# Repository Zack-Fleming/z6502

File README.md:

#Z6502

This is a collection of PCBs for a 6502-based computer. The core design of the computer is based on Ben Eater's design [here](https://eater.net/6502). I will be implementing changed to the original changes in the form of version revisions. Each board revision will have its own in-depth README.md, that will go over the changes in more depth and provide other relevant information.

This project was made using the KiCAD software, that can be downloaded [here](https://www.kicad.org/download/). If you do not have KiCAD, then there is also a zip file of the Gerber and Drill files needed to order a PCB. This zip file can be uploaded to any PCB manufacturer with no problem. 

Below the use of pinheaders is mentioned on different occasions, all of these pinheaders are of the 2.54mm pitch variety, and are the same used in the Arduino or Raspberry Pi boards as well. 

## Project Use

Use of this project is encouraged, as this is 'open-source'. I just ask to give credit to this project. 

I would like to know what others create for this project. 

## Revisions at a Glance

Revision V1:

The main changes of this version are the addition of data and control bus readouts, in the form of LEDs and pinheaders. Another change was to add PCB footprins for DIP-8 and DIP-14 type oscillators.

Currently planed Revisions:
- v2: adding a clock switching, clock dividing, halt switch, and power switch
- v3: adding another VIA chip (adding two more I/O ports)
- v4: removing the bus readouts, for miniaturization

## Modules

The computer features two 8-bit ports, that have their own headers for I/O modules. The silkscreen of the board will include all of the information for the design of the modules. This information includes: the position and size of the mounting holes, the length and width of the boards, and the position of the interface pin header. Both I/O ports are situated next to each other, and are identical in dimensions. If an I/O device needs to use both of the available ports, then one can just design a board that combines the two ports into a single board. There is no need to keep the device to only one port. 

I am currently working on a template project for KiCAD, where you can create a project from the template, instead of copy pasting the project multiple times.

Currently planed modules include:
- 1602A 16x2 character LCD screen
- 8x8 button matrix 'keyboard'
- clock switching (not an I/O module)
- LED matrix ??x??
- more.

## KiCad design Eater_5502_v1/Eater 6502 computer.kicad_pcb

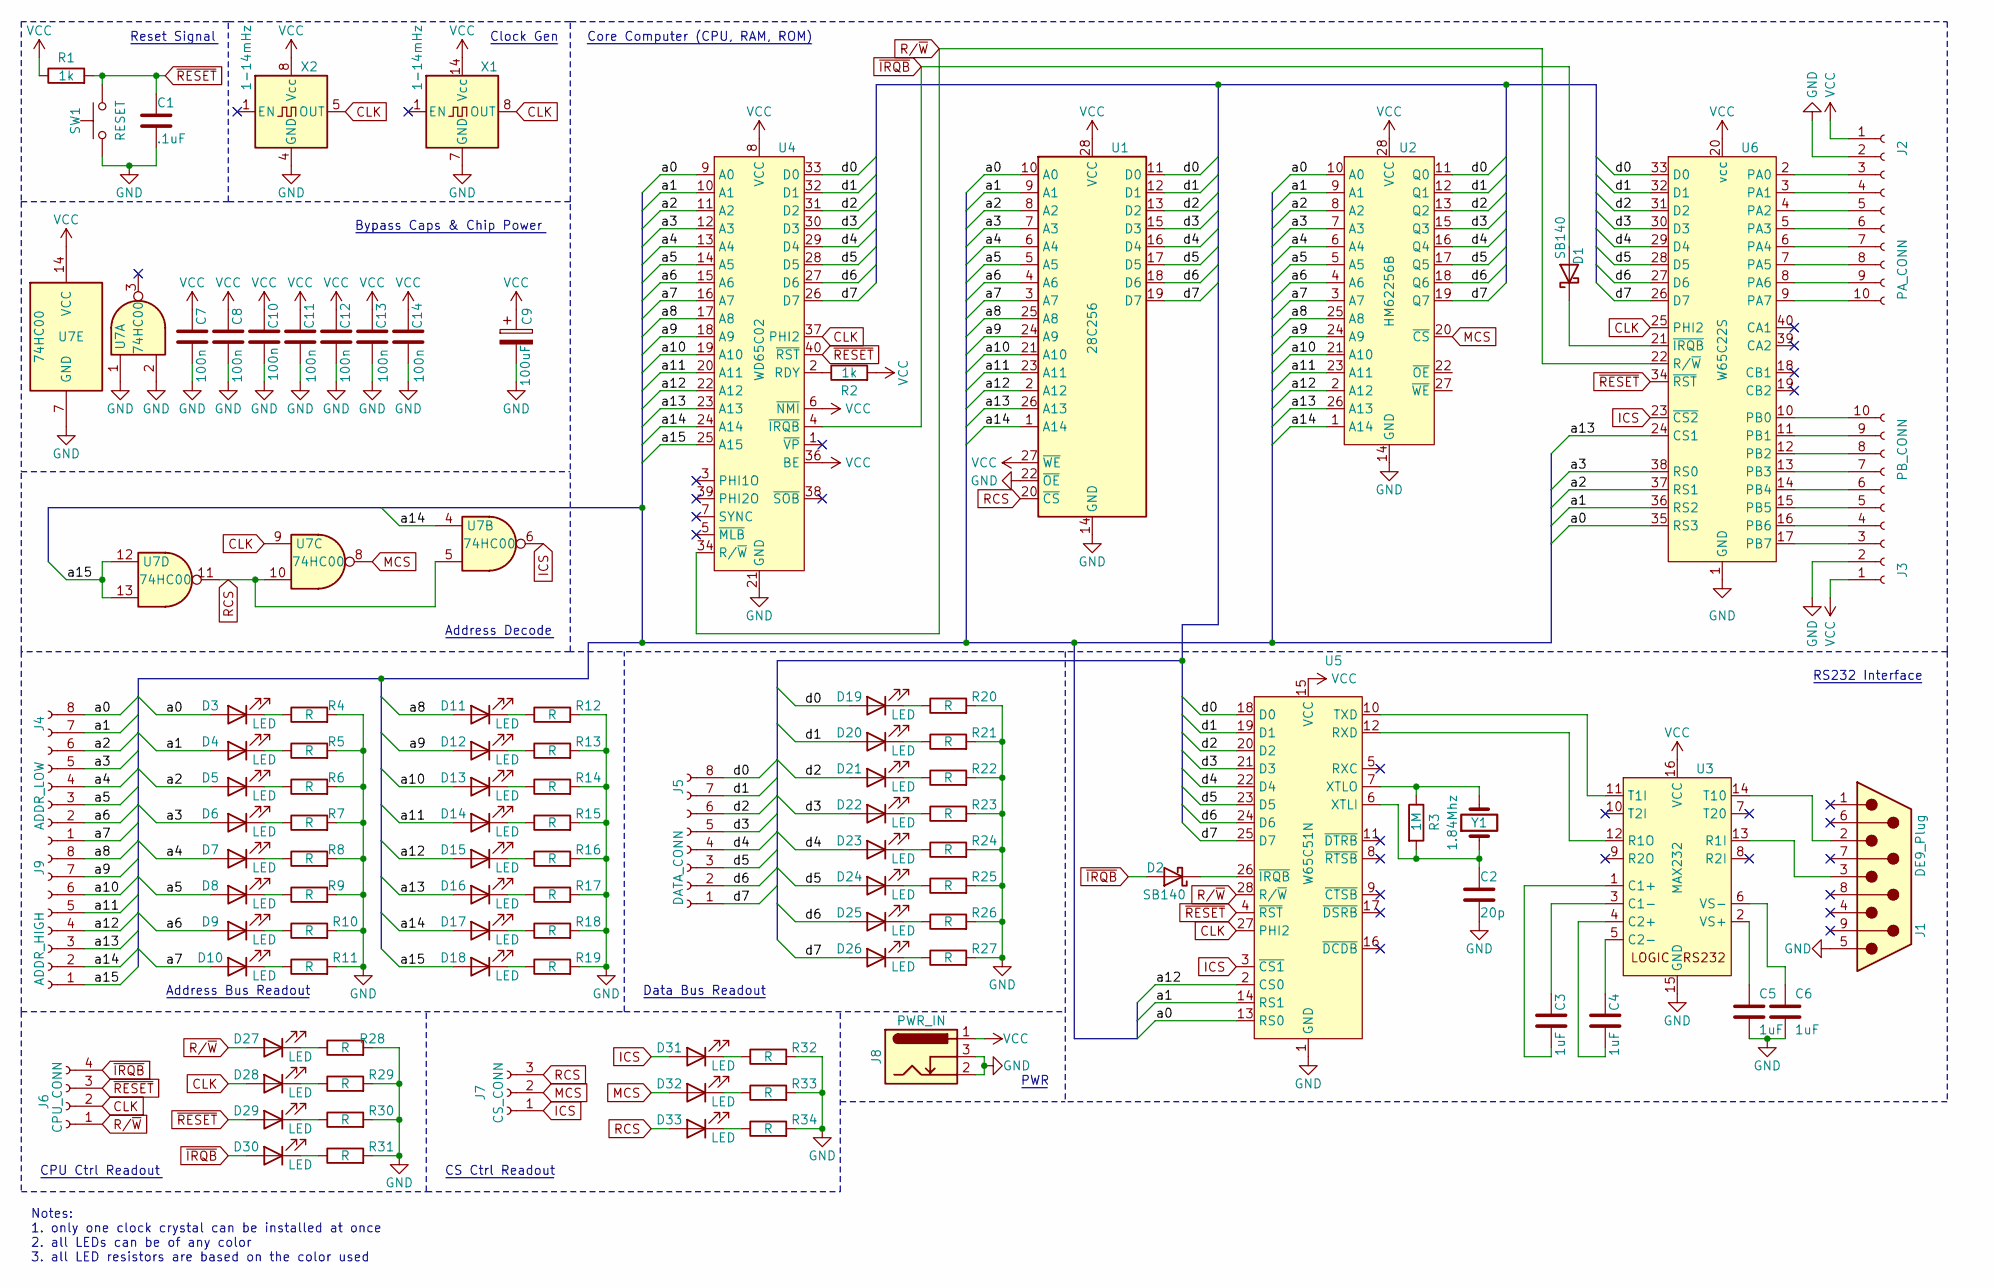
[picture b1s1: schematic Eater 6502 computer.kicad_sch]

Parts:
C1: .1uF; C_Disc_D5.0mm_W2.5mm_P5.00mm
C2: 20p; C_Disc_D5.0mm_W2.5mm_P5.00mm
C3, C4, C5, C6: 1uF; C_Disc_D5.0mm_W2.5mm_P5.00mm
C7, C8, C10, C11, C12, C13, C14: 100n; C_Disc_D5.0mm_W2.5mm_P5.00mm
C9: 100uF; CP_Radial_D5.0mm_P2.00mm
D1, D2: SB140; D_DO-41_SOD81_P10.16mm_Horizontal
D3, D4, D5, D6, D7, D8, D9, D10, D11, D12, D13, D14, D15, D16, D17, D18, D19, D20, D21, D22, D23, D24, D25, D26, D27, D28, D29, D30, D31, D32, D33: LED; LED_D5.0mm
J1: DE9_Plug; DSUB-9_Female_Horizontal_P2.77x2.84mm_EdgePinOffset9.90mm_H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
J2: PA_CONN; PinHeader_1x10_P2.54mm_Vertical
J3: PB_CONN; PinHeader_1x10_P2.54mm_Vertical
J4: ADDR_LOW; PinHeader_1x08_P2.54mm_Vertical
J5: DATA_CONN; PinHeader_1x08_P2.54mm_Vertical
J6: CPU_CONN; PinHeader_1x04_P2.54mm_Vertical
J7: CS_CONN; PinHeader_1x03_P2.54mm_Vertical
J8: PWR_IN; BarrelJack_GCT_DCJ200-10-A_Horizontal
J9: ADDR_HIGH; PinHeader_1x08_P2.54mm_Vertical
R1, R2: 1k; R_Axial_DIN0207_L6.3mm_D2.5mm_P2.54mm_Vertical
R3: 1M; R_Axial_DIN0207_L6.3mm_D2.5mm_P2.54mm_Vertical
R4, R5, R6, R7, R8, R9, R10, R11, R12, R13, R14, R15, R16, R17, R18, R19, R20, R21, R22, R23, R24, R25, R26, R27, R28, R29, R30, R31, R32, R33, R34: R; R_Axial_DIN0207_L6.3mm_D2.5mm_P2.54mm_Vertical
SW1: RESET; SW_PUSH_6mm
U1: 28C256; DIP-28_W15.24mm_Socket_LongPads
U2: HM62256B; DIP-28_W15.24mm_Socket_LongPads
U3: MAX232; DIP-16_W7.62mm_Socket_LongPads
U4: WD65C02; DIP-40_W15.24mm_Socket_LongPads
U5: W65C51N; DIP-28_W15.24mm_Socket_LongPads
U6: W65C22S; DIP-40_W15.24mm_Socket_LongPads
U7: 74HC00; DIP-14_W7.62mm_Socket_LongPads
X1: 1-14mHz; Oscillator_DIP-14
X2: 1-14mHz; Oscillator_DIP-8
Y1: 1.84Mhz; Crystal_HC49-4H_Vertical

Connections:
/a0: D3.2 (A), J4.8, U1.10 (A0), U2.10 (A0), U4.9 (A0), U5.13 (RS0), U6.35 (RS3)
/a1: D4.2 (A), J4.7, U1.9 (A1), U2.9 (A1), U4.10 (A1), U5.14 (RS1), U6.36 (RS2)
/a2: D5.2 (A), J4.6, U1.8 (A2), U2.8 (A2), U4.11 (A2), U6.37 (RS1)
/a3: D6.2 (A), J4.5, U1.7 (A3), U2.7 (A3), U4.12 (A3), U6.38 (RS0)
/a4: D7.2 (A), J4.4, U1.6 (A4), U2.6 (A4), U4.13 (A4)
/a5: D8.2 (A), J4.3, U1.5 (A5), U2.5 (A5), U4.14 (A5)
/a6: D9.2 (A), J4.2, U1.4 (A6), U2.4 (A6), U4.15 (A6)
/a7: D10.2 (A), J4.1, U1.3 (A7), U2.3 (A7), U4.16 (A7)
/a8: D11.2 (A), J9.8, U1.25 (A8), U2.25 (A8), U4.17 (A8)
/a9: D12.2 (A), J9.7, U1.24 (A9), U2.24 (A9), U4.18 (A9)
/a10: D13.2 (A), J9.6, U1.21 (A10), U2.21 (A10), U4.19 (A10)
/a11: D14.2 (A), J9.5, U1.23 (A11), U2.23 (A11), U4.20 (A11)
/a12: D15.2 (A), J9.4, U1.2 (A12), U2.2 (A12), U4.22 (A12), U5.2 (CS0)
/a13: D16.2 (A), J9.3, U1.26 (A13), U2.26 (A13), U4.23 (A13), U6.24 (CS1)
/a14: D17.2 (A), J9.2, U1.1 (A14), U2.1 (A14), U4.24 (A14), U7.4
/a15: D18.2 (A), J9.1, U4.25 (A15), U7.12, U7.13
/d0: D19.2 (A), J5.8, U1.11 (D0), U2.11 (Q0), U4.33 (D0), U5.18 (D0), U6.33 (D0)
/d1: D20.2 (A), J5.7, U1.12 (D1), U2.12 (Q1), U4.32 (D1), U5.19 (D1), U6.32 (D1)
/d2: D21.2 (A), J5.6, U1.13 (D2), U2.13 (Q2), U4.31 (D2), U5.20 (D2), U6.31 (D2)
/d3: D22.2 (A), J5.5, U1.15 (D3), U2.15 (Q3), U4.30 (D3), U5.21 (D3), U6.30 (D3)
/d4: D23.2 (A), J5.4, U1.16 (D4), U2.16 (Q4), U4.29 (D4), U5.22 (D4), U6.29 (D4)
/d5: D24.2 (A), J5.3, U1.17 (D5), U2.17 (Q5), U4.28 (D5), U5.23 (D5), U6.28 (D5)
/d6: D25.2 (A), J5.2, U1.18 (D6), U2.18 (Q6), U4.27 (D6), U5.24 (D6), U6.27 (D6)
/d7: D26.2 (A), J5.1, U1.19 (D7), U2.19 (Q7), U4.26 (D7), U5.25 (D7), U6.26 (D7)
CLK: D28.2 (A), J6.2, U4.37 (PHI2), U5.27 (PHI2), U6.25 (PHI2), U7.9, X1.8 (OUT), X2.5 (OUT)
GND: C1.2, C2.2, C5.2, C6.2, C7.2, C8.2, C9.2, C10.2, C11.2, C12.2, C13.2, C14.2, J1.0, J1.5, J2.2, J3.2, J8.2, J8.3, R4.2, R5.2, R6.2, R7.2, R8.2, R9.2, R10.2, R11.2, R12.2, R13.2, R14.2, R15.2, R16.2, R17.2, R18.2, R19.2, R20.2, R21.2, R22.2, R23.2, R24.2, R25.2, R26.2, R27.2, R28.2, R29.2, R30.2, R31.2, R32.2, R33.2, R34.2, SW1.1, U1.14 (GND), U1.22 (~OE), U2.14 (GND), U3.15 (GND), U4.21 (GND), U5.1 (GND), U6.1 (GND), U7.1, U7.2, U7.7 (GND), X1.7 (GND), X2.4 (GND)
ICS: D31.2 (A), J7.1, U5.3 (~CS1), U6.23 (~CS2), U7.6
MCS: D32.2 (A), J7.2, U2.20 (~CS), U7.8
unnamed: D1.1 (K), U6.21 (~IRQB)
unnamed: D2.1 (K), U5.26 (~IRQB)
unnamed: D3.1 (K), R4.1
unnamed: D4.1 (K), R5.1
unnamed: D5.1 (K), R6.1
unnamed: D6.1 (K), R7.1
unnamed: D7.1 (K), R8.1
unnamed: D8.1 (K), R9.1
unnamed: D9.1 (K), R10.1
unnamed: D10.1 (K), R11.1
unnamed: D11.1 (K), R12.1
unnamed: D12.1 (K), R13.1
unnamed: D13.1 (K), R14.1
unnamed: D14.1 (K), R15.1
unnamed: D15.1 (K), R16.1
unnamed: D16.1 (K), R17.1
unnamed: D17.1 (K), R18.1
unnamed: D18.1 (K), R19.1
unnamed: D19.1 (K), R20.1
unnamed: D20.1 (K), R21.1
unnamed: D21.1 (K), R22.1
unnamed: D22.1 (K), R23.1
unnamed: D23.1 (K), R24.1
unnamed: D24.1 (K), R25.1
unnamed: D25.1 (K), R26.1
unnamed: D26.1 (K), R27.1
unnamed: D27.1 (K), R28.1
unnamed: D28.1 (K), R29.1
unnamed: D29.1 (K), R30.1
unnamed: D30.1 (K), R31.1
unnamed: D31.1 (K), R32.1
unnamed: D32.1 (K), R33.1
unnamed: D33.1 (K), R34.1
unnamed: J2.3, U6.2 (PA0)
unnamed: J2.4, U6.3 (PA1)
unnamed: J2.5, U6.4 (PA2)
unnamed: J2.6, U6.5 (PA3)
unnamed: J2.7, U6.6 (PA4)
unnamed: J2.8, U6.7 (PA5)
unnamed: J2.9, U6.8 (PA6)
unnamed: J2.10, U6.9 (PA7)
unnamed: J3.3, U6.17 (PB7)
unnamed: J3.4, U6.16 (PB6)
unnamed: J3.5, U6.15 (PB5)
unnamed: J3.6, U6.14 (PB4)
unnamed: J3.7, U6.13 (PB3)
unnamed: J3.8, U6.12 (PB2)
unnamed: J3.9, U6.11 (PB1)
unnamed: J3.10, U6.10 (PB0)
unnamed: C3.2, U3.1 (C1+)
unnamed: C3.1, U3.3 (C1-)
unnamed: C4.2, U3.4 (C2+)
unnamed: C4.1, U3.5 (C2-)
unnamed: J1.3, U3.13 (R1I)
unnamed: U3.12 (R1O), U5.12 (RXD)
unnamed: U3.11 (T1I), U5.10 (TXD)
unnamed: J1.2, U3.14 (T10)
unnamed: C5.1, U3.2 (VS+)
unnamed: C6.1, U3.6 (VS-)
unnamed: R2.1, U4.2 (RDY)
unnamed: C2.1, R3.2, U5.6 (XTLI), Y1.1
unnamed: R3.1, U5.7 (XTLO), Y1.2
RCS: D33.2 (A), J7.3, U1.20 (~CS), U7.5, U7.10, U7.11
R/~W: D27.2 (A), J6.1, U4.34 (R/~W), U5.28 (R/~W), U6.22 (R/~W)
VCC: C7.1, C8.1, C9.1, C10.1, C11.1, C12.1, C13.1, C14.1, J2.1, J3.1, J8.1, R1.1, R2.2, U1.27 (~WE), U1.28 (VCC), U2.28 (VCC), U3.16 (VCC), U4.6 (~NMI), U4.8 (VCC), U4.36 (BE), U5.15 (VCC), U6.20 (vcc), U7.14 (VCC), X1.14 (Vcc), X2.8 (Vcc)
~IRQB: D1.2 (A), D2.2 (A), D30.2 (A), J6.4, U4.4 (~IRQB)
~RESET: C1.1, D29.2 (A), J6.3, R1.2, SW1.2, U4.40 (~RST), U5.4 (~RST), U6.34 (~RST)

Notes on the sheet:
Address Decode ~{ }
CPU Ctrl Readout ~{ }
Notes: 1. only one clock crystal can be installed at once 2. all LEDs can be of any color 3. all LED resistors are based on the color used
Core Computer (CPU, RAM, ROM) ~{ }
Clock Gen ~{ }
Data Bus Readout ~{ }
RS232 Interface ~{ }
Reset Signal ~{ }
CS Ctrl Readout ~{ }
PWR ~{ }
Address Bus Readout ~{ }
Bypass Caps & Chip Power ~{ }

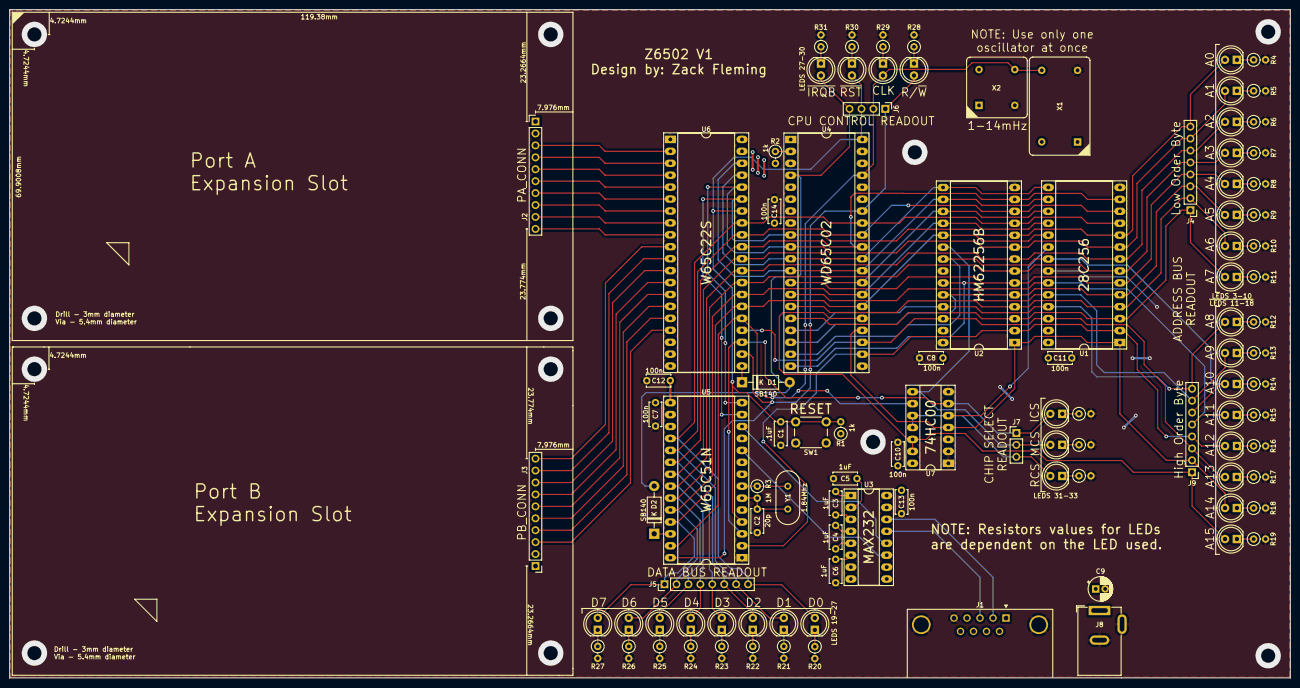
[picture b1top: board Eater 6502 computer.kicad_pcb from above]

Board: 2 copper layers, 272.7 x 142.3 mm, 101 parts (0 on the bottom side), 95 nets.

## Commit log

2024-05-18 finish v1 of main board
2024-05-18 Update README.md - Added Project Use section and added planed versions
2024-05-27 updated board design to include bigger capacitor footprints, added the bulk decoupling cap to the power input, and made text larger in places to improve readability
